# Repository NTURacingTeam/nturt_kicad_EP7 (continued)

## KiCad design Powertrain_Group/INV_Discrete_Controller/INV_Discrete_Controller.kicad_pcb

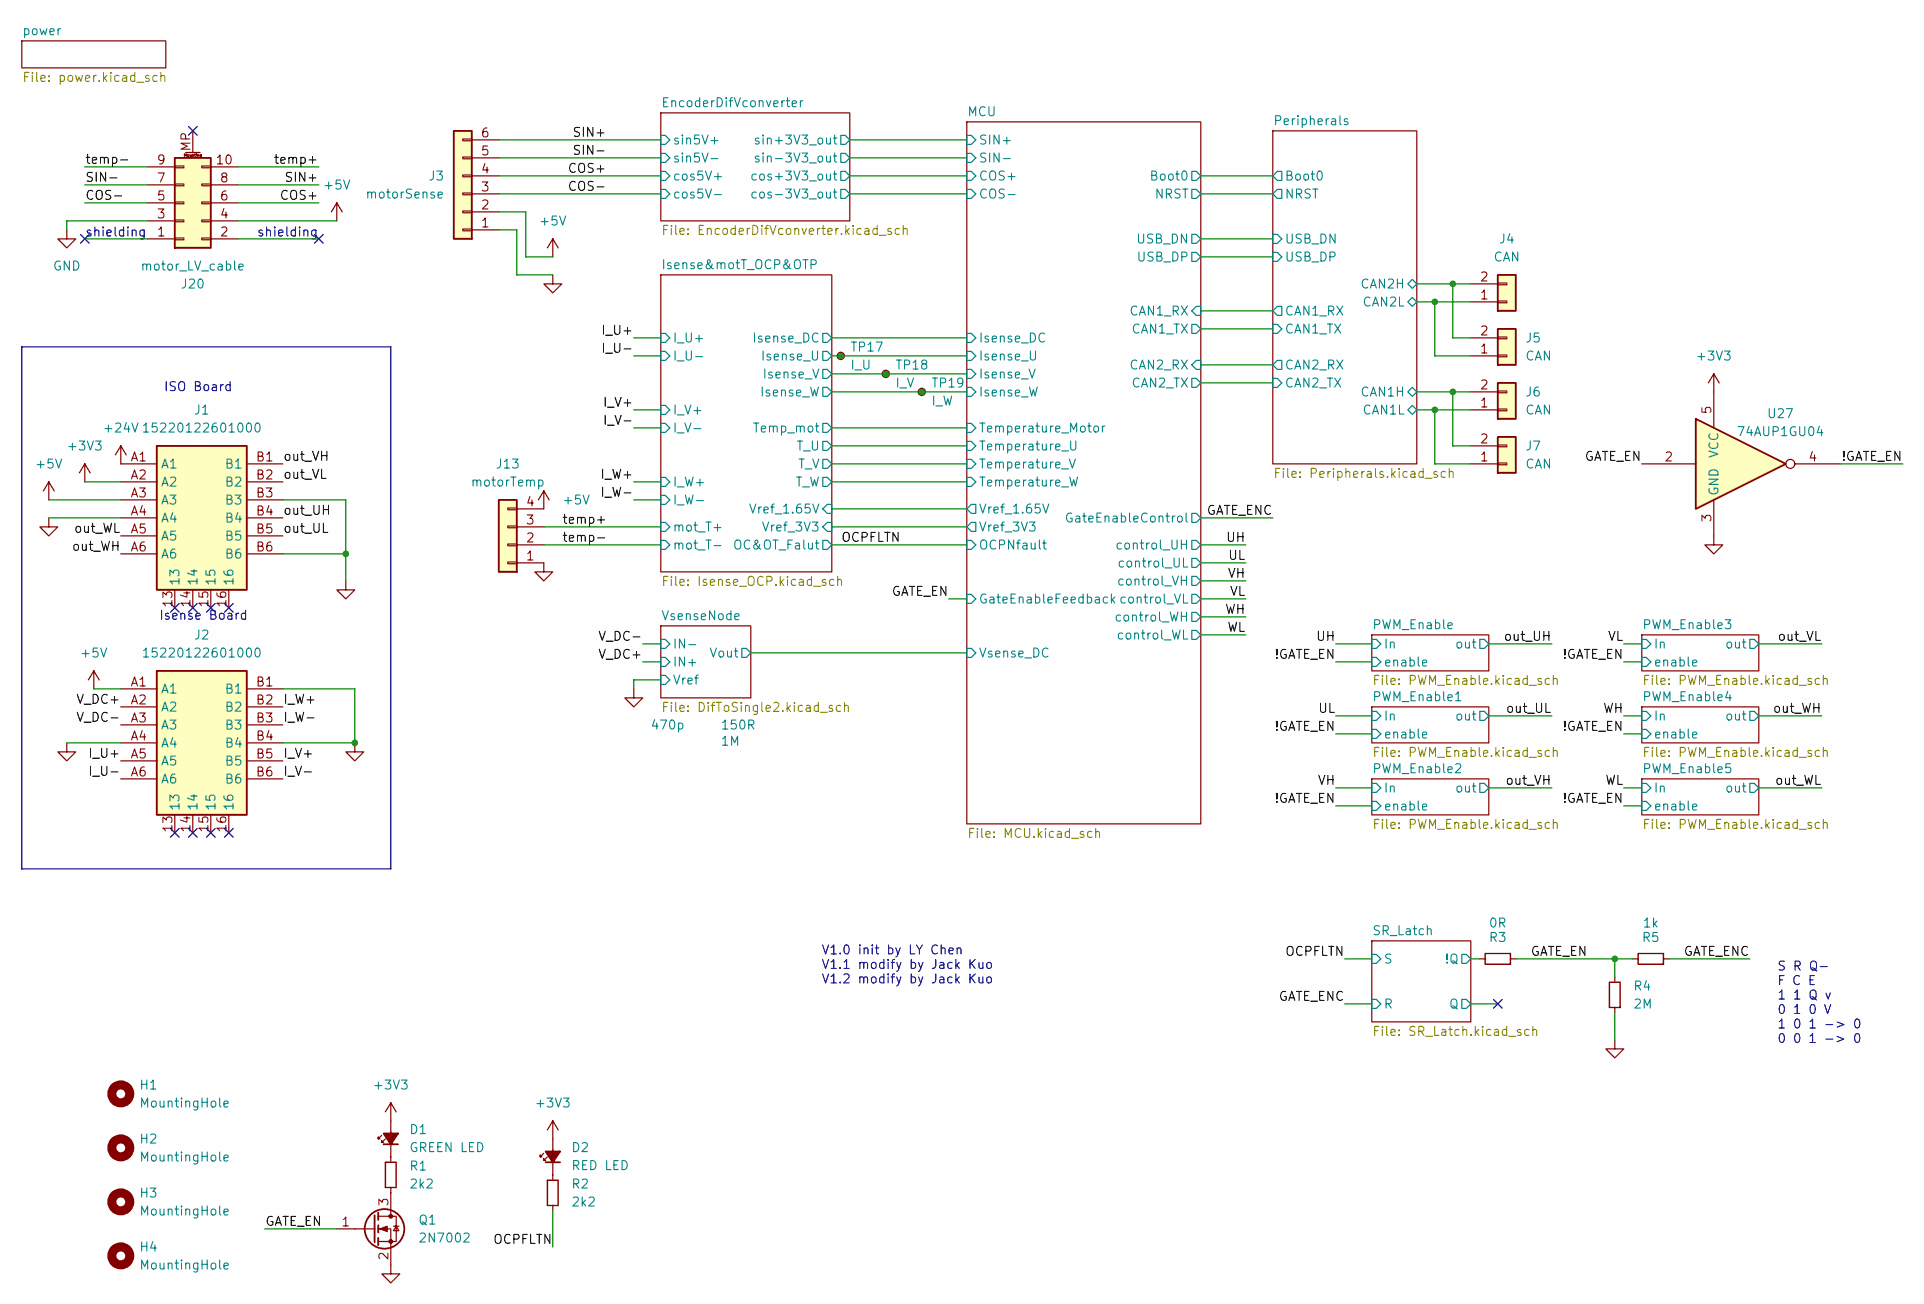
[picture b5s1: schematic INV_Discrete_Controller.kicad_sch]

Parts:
D1: GREEN LED; LED_0805_2012Metric
D2: RED LED; LED_0805_2012Metric
H1, H2, H3, H4: MountingHole; MountingHole_3.2mm_M3
J1, J2: 15220122601000; Harting_15220122601000; Mouser Part Number 617-15130122601000
J3: motorSense; JST_XH_B6B-XH-A_1x06_P2.50mm_Vertical
J4, J5, J6, J7: CAN; JST_XH_B2B-XH-A_1x02_P2.50mm_Vertical
J13: motorTemp; JST_XH_B4B-XH-A_1x04_P2.50mm_Vertical
J20: motor_LV_cable; CONN_2202010000-SD_10P_MOL
Q1: 2N7002; SOT-23
R1, R2: 2k2; R_0402_1005Metric
R3: 0R; R_0402_1005Metric
R4: 2M; R_0603_1608Metric
R5: 1k; R_0402_1005Metric
TP17: I_U; TestPoint_Pad_D1.0mm
TP18: I_V; TestPoint_Pad_D1.0mm
TP19: I_W; TestPoint_Pad_D1.0mm
U27: 74AUP1GU04; SOT-23-5

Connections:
+3V3: D1.2 (A), D2.2 (A), J1.A2, U27.5 (VCC); also elsewhere on the board
+5V: J1.A3, J2.A1, J3.2, J13.4, J20.4; also elsewhere on the board
+24V: J1.A1; also elsewhere on the board
/!GATE_EN: U27.4; also elsewhere on the board
/COS+: J3.4, J20.6; also elsewhere on the board
/COS-: J3.3, J20.5; also elsewhere on the board
/GATE_EN: Q1.1 (G), R3.1, R4.2, R5.2, U27.2; also elsewhere on the board
/GATE_ENC: R5.1; also elsewhere on the board
/I_U+: J2.A5; also elsewhere on the board
/I_U-: J2.A6; also elsewhere on the board
/I_V+: J2.B5; also elsewhere on the board
/I_V-: J2.B6; also elsewhere on the board
/I_W+: J2.B2; also elsewhere on the board
/I_W-: J2.B3; also elsewhere on the board
/Isense&motT_OCP&OTP/Isense_U: TP17.1; also elsewhere on the board
/Isense&motT_OCP&OTP/Isense_V: TP18.1; also elsewhere on the board
/Isense&motT_OCP&OTP/Isense_W: TP19.1; also elsewhere on the board
/OCPFLTN: R2.2; also elsewhere on the board
/Peripherals/CAN1H: J6.2, J7.2; also elsewhere on the board
/Peripherals/CAN1L: J6.1, J7.1; also elsewhere on the board
/Peripherals/CAN2H: J4.2, J5.2; also elsewhere on the board
/Peripherals/CAN2L: J4.1, J5.1; also elsewhere on the board
/SIN+: J3.6, J20.8; also elsewhere on the board
/SIN-: J3.5, J20.7; also elsewhere on the board
/SR_Latch/!Q: R3.2; also elsewhere on the board
/V_DC+: J2.A2; also elsewhere on the board
/V_DC-: J2.A3; also elsewhere on the board
/out_UH: J1.B4; also elsewhere on the board
/out_UL: J1.B5; also elsewhere on the board
/out_VH: J1.B1; also elsewhere on the board
/out_VL: J1.B2; also elsewhere on the board
/out_WH: J1.A6; also elsewhere on the board
/out_WL: J1.A5; also elsewhere on the board
/temp+: J13.3, J20.10; also elsewhere on the board
/temp-: J13.2, J20.9; also elsewhere on the board
GND: J1.A4, J1.B3, J1.B6, J2.A4, J2.B1, J2.B4, J3.1, J13.1, J20.3, Q1.2 (S), R4.1, U27.3 (GND); also elsewhere on the board
unnamed: D1.1 (K), R1.1
unnamed: D2.1 (K), R2.1
unnamed: Q1.3 (D), R1.2

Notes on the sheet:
shielding
V1.0 init by LY Chen V1.1 modify by Jack Kuo V1.2 modify by Jack Kuo
Isense Board
S R Q- F C E 1 1 Q v 0 1 0 V 1 0 1 -> 0 0 0 1 -> 0
ISO Board

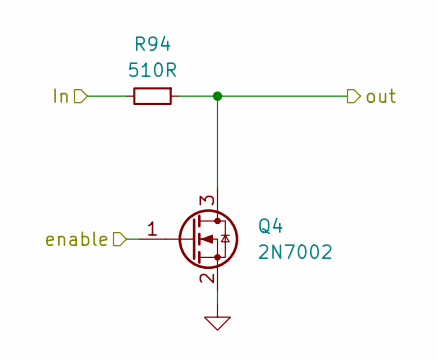
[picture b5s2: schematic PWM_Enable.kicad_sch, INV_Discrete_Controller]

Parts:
Q4: 2N7002; SOT-23
R94: 510R; R_0603_1608Metric

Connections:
/!GATE_EN: Q4.1 (G); also elsewhere on the board
/UH: R94.2; also elsewhere on the board
/out_UH: Q4.3 (D), R94.1; also elsewhere on the board
GND: Q4.2 (S); also elsewhere on the board

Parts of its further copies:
Q2, Q3, Q5, Q6, Q7: 2N7002; SOT-23
R80, R93, R98, R99, R100: 510R; R_0603_1608Metric

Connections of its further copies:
/!GATE_EN: Q2.1 (G), Q3.1 (G), Q5.1 (G), Q6.1 (G), Q7.1 (G); also elsewhere on the board
/UL: R80.2; also elsewhere on the board
/VH: R93.2; also elsewhere on the board
/VL: R98.2; also elsewhere on the board
/WH: R99.2; also elsewhere on the board
/WL: R100.2; also elsewhere on the board
/out_UL: Q2.3 (D), R80.1; also elsewhere on the board
/out_VH: Q3.3 (D), R93.1; also elsewhere on the board
/out_VL: Q5.3 (D), R98.1; also elsewhere on the board
/out_WH: Q6.3 (D), R99.1; also elsewhere on the board
/out_WL: Q7.3 (D), R100.1; also elsewhere on the board
GND: Q2.2 (S), Q3.2 (S), Q5.2 (S), Q6.2 (S), Q7.2 (S); also elsewhere on the board

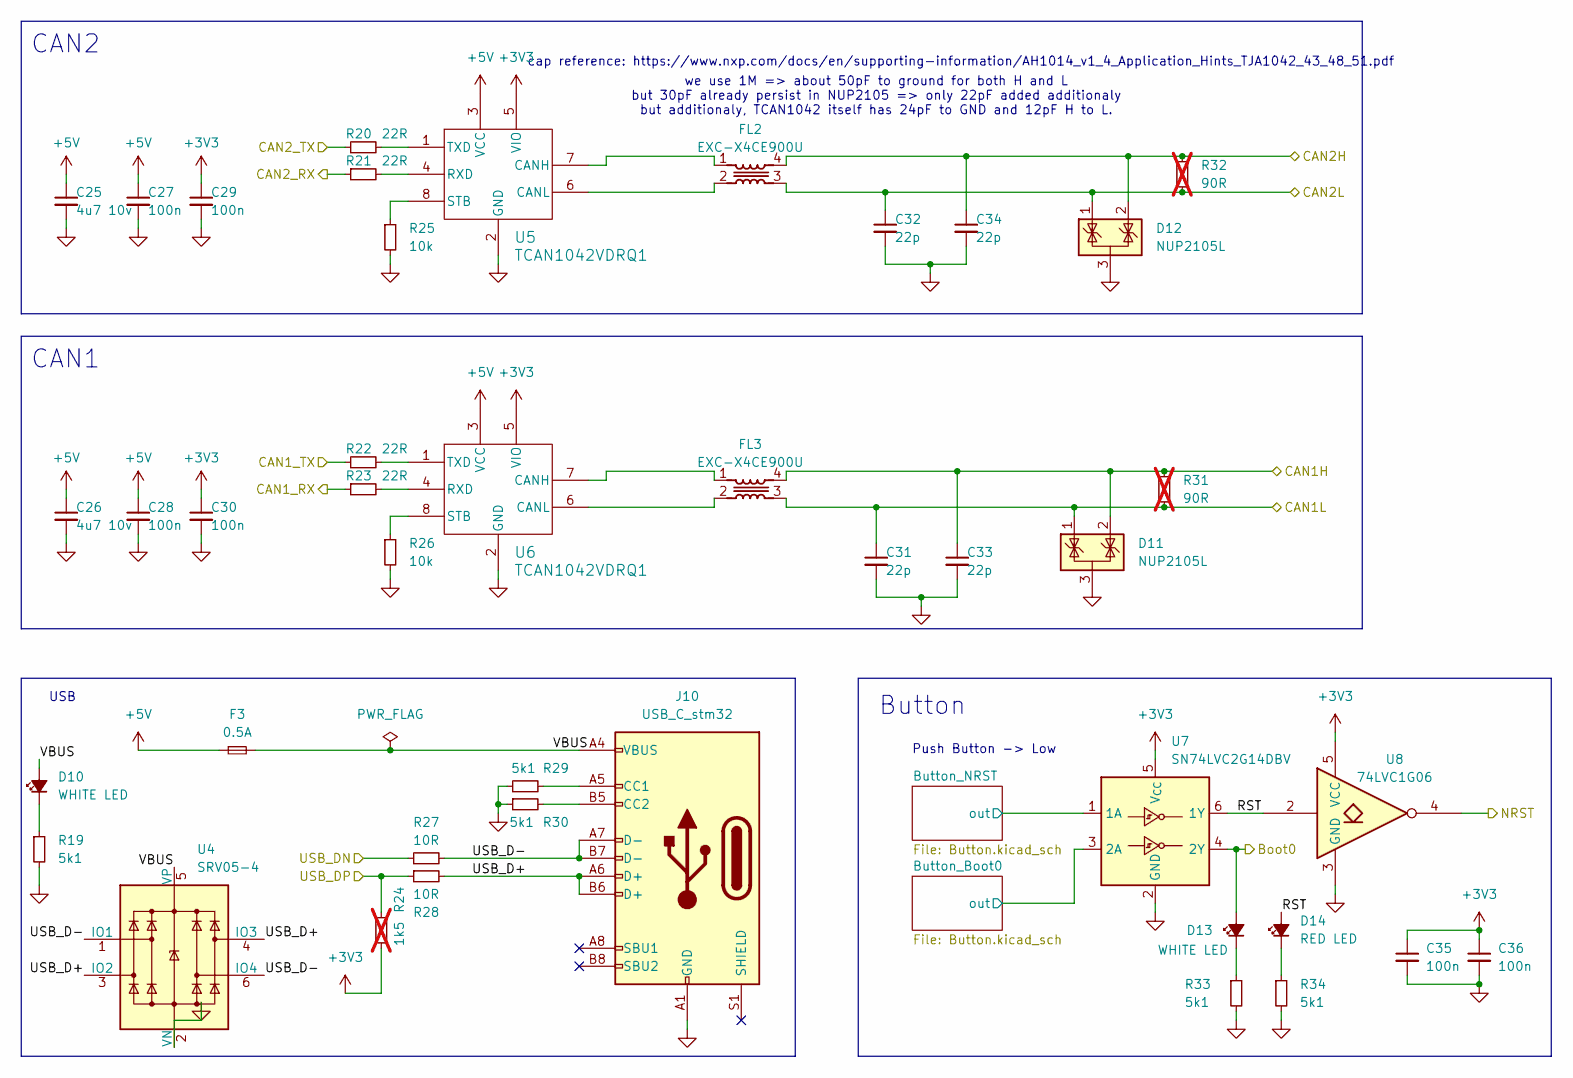
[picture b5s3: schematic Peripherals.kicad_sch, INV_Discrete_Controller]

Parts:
C25, C26: 4u7 10v; C_0402_1005Metric
C27, C28, C29, C30, C35, C36: 100n; C_0402_1005Metric
C31, C32, C33, C34: 22p; C_0402_1005Metric
D10, D13: WHITE LED; LED_0603_1608Metric
D11, D12: NUP2105L; SOT-23
D14: RED LED; LED_0603_1608Metric
F3: 0.5A; Fuse_1206_3216Metric
FL2, FL3: EXC-X4CE900U; EXCX4CE900U; Mouser Part Number 667-EXC-X4CE900U
J10: USB_C_stm32; USB_C_Receptacle_GCT_USB4105-xx-A_16P_TopMnt_Horizontal
R19, R29, R30, R33, R34: 5k1; R_0402_1005Metric
R20, R21, R22, R23: 22R; R_0402_1005Metric
R24: 1k5; R_0402_1005Metric; not fitted
R25, R26: 10k; R_0402_1005Metric
R27, R28: 10R; R_0402_1005Metric
R31, R32: 90R; R_0402_1005Metric; not fitted
U4: SRV05-4; SOT-23-6
U5, U6: TCAN1042VDRQ1; SOIC-8_3.9x4.9mm_P1.27mm
U7: SN74LVC2G14DBV; SOT-23-6
U8: 74LVC1G06; SOT-23-5

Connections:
+3V3: C29.1, C30.1, C35.1, C36.1, R24.1, U5.5 (VIO), U6.5 (VIO), U7.5 (V_{CC}), U8.5 (VCC); also elsewhere on the board
+5V: C25.1, C26.1, C27.1, C28.1, F3.1, U5.3 (VCC), U6.3 (VCC); also elsewhere on the board
/MCU/Boot0: D13.2 (A), U7.4 (2Y); also elsewhere on the board
/MCU/CAN1_RX: R23.1; also elsewhere on the board
/MCU/CAN1_TX: R22.1; also elsewhere on the board
/MCU/CAN2_RX: R21.1; also elsewhere on the board
/MCU/CAN2_TX: R20.1; also elsewhere on the board
/MCU/NRST: U8.4; also elsewhere on the board
/MCU/USB_DN: R27.1; also elsewhere on the board
/MCU/USB_DP: R24.2, R28.1; also elsewhere on the board
/Peripherals/Button_Boot0/out: U7.3 (2A); also elsewhere on the board
/Peripherals/Button_NRST/out: U7.1 (1A); also elsewhere on the board
/Peripherals/CAN1H: C33.1, D11.2 (K), FL3.4, R31.1; also elsewhere on the board
/Peripherals/CAN1L: C31.1, D11.1 (K), FL3.3, R31.2; also elsewhere on the board
/Peripherals/CAN2H: C34.1, D12.2 (K), FL2.4, R32.1; also elsewhere on the board
/Peripherals/CAN2L: C32.1, D12.1 (K), FL2.3, R32.2; also elsewhere on the board
/Peripherals/RST: D14.2 (A), U7.6 (1Y), U8.2
/Peripherals/USB_D+: J10.A6 (D+), J10.B6 (D+), R28.2, U4.3 (IO2), U4.4 (IO3)
/Peripherals/USB_D-: J10.A7 (D-), J10.B7 (D-), R27.2, U4.1 (IO1), U4.6 (IO4)
/Peripherals/VBUS: D10.2 (A), F3.2, J10.A4 (VBUS), J10.A9 (VBUS), J10.B4 (VBUS), J10.B9 (VBUS), U4.5 (VP)
GND: C25.2, C26.2, C27.2, C28.2, C29.2, C30.2, C31.2, C32.2, C33.2, C34.2, C35.2, C36.2, D11.3 (A), D12.3 (A), J10.A1 (GND), J10.A12 (GND), J10.B1 (GND), J10.B12 (GND), R19.2, R25.2, R26.2, R29.1, R30.1, R33.2, R34.2, U4.2 (VN), U5.2 (GND), U6.2 (GND), U7.2 (GND), U8.3 (GND); also elsewhere on the board
unnamed: D10.1 (K), R19.1
unnamed: D13.1 (K), R33.1
unnamed: D14.1 (K), R34.1
unnamed: J10.A5 (CC1), R29.2
unnamed: J10.B5 (CC2), R30.2
unnamed: FL2.1, U5.7 (CANH)
unnamed: FL2.2, U5.6 (CANL)
unnamed: R21.2, U5.4 (RXD)
unnamed: R25.1, U5.8 (STB)
unnamed: R20.2, U5.1 (TXD)
unnamed: FL3.1, U6.7 (CANH)
unnamed: FL3.2, U6.6 (CANL)
unnamed: R23.2, U6.4 (RXD)
unnamed: R26.1, U6.8 (STB)
unnamed: R22.2, U6.1 (TXD)

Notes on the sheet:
Push Button -> Low
Button
USB
we use 1M => about 50pF to ground for both H and L but 30pF already persist in NUP2105 => only 22pF added additionaly but additionaly, TCAN1042 itself has 24pF to GND and 12pF H to L.
CAN2
CAN1
cap reference: https://www.nxp.com/docs/en/supporting-information/AH1014_v1_4_Application_Hints_TJA1042_43_48_51.pdf

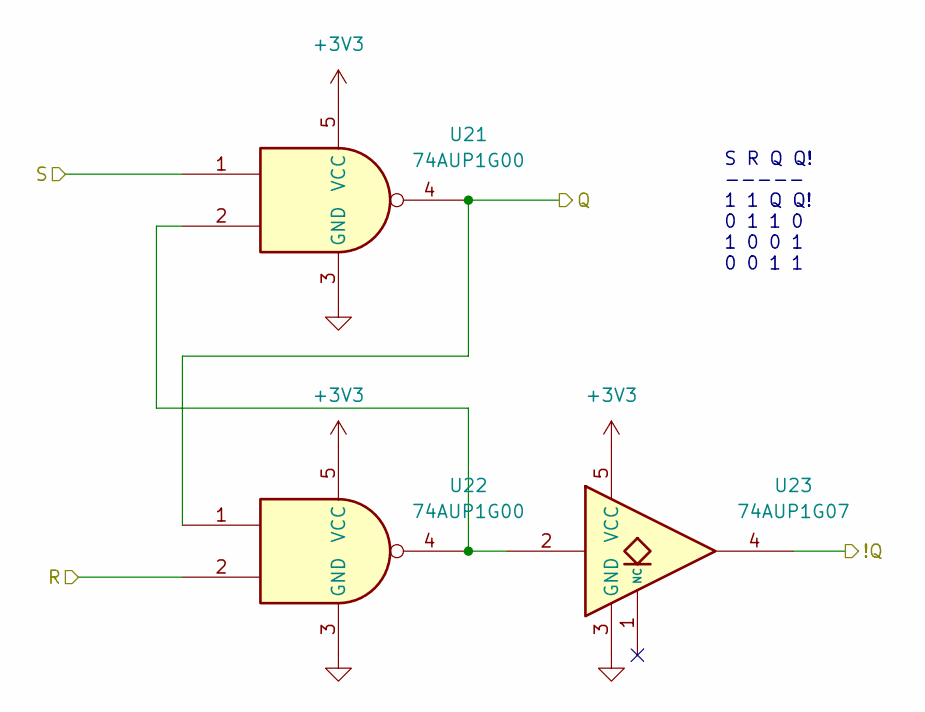
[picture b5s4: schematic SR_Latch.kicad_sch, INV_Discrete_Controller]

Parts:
U21, U22: 74AUP1G00; SOT-23-5
U23: 74AUP1G07; SOT-23-5

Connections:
+3V3: U21.5 (VCC), U22.5 (VCC), U23.5 (VCC); also elsewhere on the board
/GATE_ENC: U22.2; also elsewhere on the board
/OCPFLTN: U21.1; also elsewhere on the board
/SR_Latch/!Q: U23.4; also elsewhere on the board
/SR_Latch/Q: U21.4, U22.1
GND: U21.3 (GND), U22.3 (GND), U23.3 (GND); also elsewhere on the board
unnamed: U21.2, U22.4, U23.2

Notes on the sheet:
S R Q Q! ----- 1 1 Q Q! 0 1 1 0 1 0 0 1 0 0 1 1

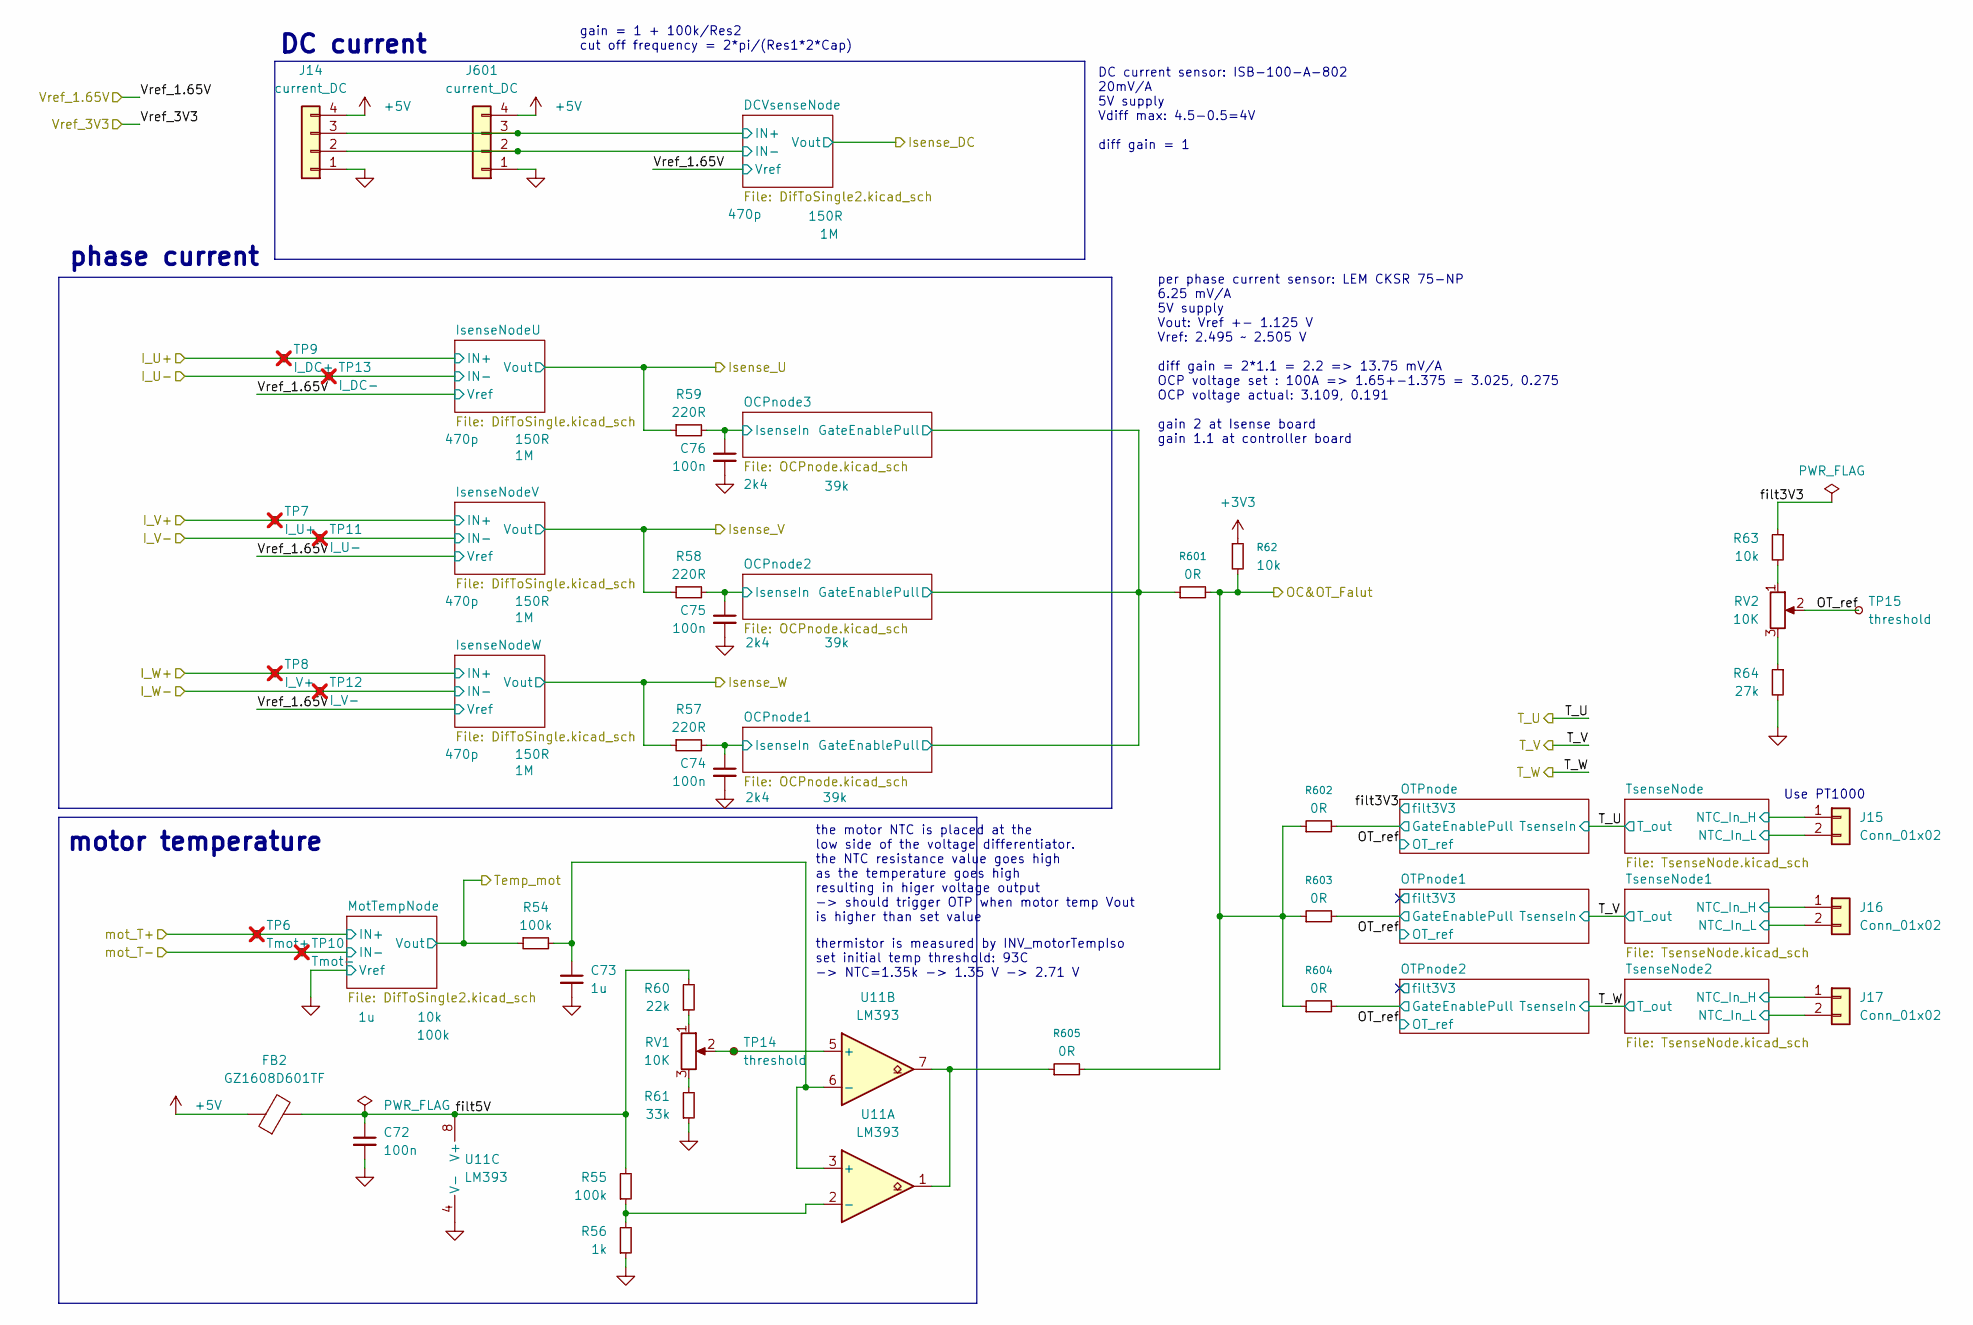
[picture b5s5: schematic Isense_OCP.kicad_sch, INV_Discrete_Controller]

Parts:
C72, C74, C75, C76: 100n; C_0402_1005Metric
C73: 1u; C_0402_1005Metric
FB2: GZ1608D601TF; C_0603_1608Metric
J14: current_DC; JST_XH_B4B-XH-A_1x04_P2.50mm_Vertical; Part Number 1-0401FBV0T
J15, J16, J17: Conn_01x02; JST_PH_B2B-PH-K_1x02_P2.00mm_Vertical
J601: current_DC; JST_PH_B4B-PH-K_1x04_P2.00mm_Vertical; Part Number 1-0401FBV0T
R54, R55: 100k; R_0402_1005Metric
R56: 1k; R_0402_1005Metric
R57, R58, R59: 220R; R_0402_1005Metric
R60: 22k; R_0402_1005Metric
R61: 33k; R_0402_1005Metric
R62, R63: 10k; R_0402_1005Metric
R64: 27k; R_0402_1005Metric
R601, R602, R603, R604, R605: 0R; R_0402_1005Metric
RV1, RV2: 10K; Potentiometer_Bourns_3296W_Horizontal
TP6: Tmot+; TestPoint_Pad_D1.0mm; not fitted
TP7: I_U+; TestPoint_Pad_D1.0mm; not fitted
TP8: I_V+; TestPoint_Pad_D1.0mm; not fitted
TP9: I_DC+; TestPoint_Pad_D1.0mm; not fitted
TP10: Tmot-; TestPoint_Pad_D1.0mm; not fitted
TP11: I_U-; TestPoint_Pad_D1.0mm; not fitted
TP12: I_V-; TestPoint_Pad_D1.0mm; not fitted
TP13: I_DC-; TestPoint_Pad_D1.0mm; not fitted
TP14, TP15: threshold; TestPoint_Pad_D1.0mm
U11: LM393; SOIC-8_3.9x4.9mm_P1.27mm

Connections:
+3V3: R62.1; also elsewhere on the board
+5V: FB2.1, J14.4, J601.4; also elsewhere on the board
/Isense&motT_OCP&OTP/DCVsenseNode/IN+: J14.3, J601.3; also elsewhere on the board
/Isense&motT_OCP&OTP/DCVsenseNode/IN-: J14.2, J601.2; also elsewhere on the board
/Isense&motT_OCP&OTP/Isense_U: R59.1; also elsewhere on the board
/Isense&motT_OCP&OTP/Isense_V: R58.1; also elsewhere on the board
/Isense&motT_OCP&OTP/Isense_W: R57.1; also elsewhere on the board
/Isense&motT_OCP&OTP/OCPnode1/GateEnablePull: R601.1; also elsewhere on the board
/Isense&motT_OCP&OTP/OCPnode1/IsenseIn: C74.1, R57.2; also elsewhere on the board
/Isense&motT_OCP&OTP/OCPnode2/IsenseIn: C75.1, R58.2; also elsewhere on the board
/Isense&motT_OCP&OTP/OCPnode3/IsenseIn: C76.1, R59.2; also elsewhere on the board
/Isense&motT_OCP&OTP/OTPnode1/GateEnablePull: R603.2; also elsewhere on the board
/Isense&motT_OCP&OTP/OTPnode2/GateEnablePull: R604.2; also elsewhere on the board
/Isense&motT_OCP&OTP/OTPnode/GateEnablePull: R602.2; also elsewhere on the board
/Isense&motT_OCP&OTP/OT_ref: RV2.2, TP15.1; also elsewhere on the board
/Isense&motT_OCP&OTP/Temp_mot: R54.1; also elsewhere on the board
/Isense&motT_OCP&OTP/TsenseNode1/NTC_In_H: J16.1; also elsewhere on the board
/Isense&motT_OCP&OTP/TsenseNode2/NTC_In_H: J17.1; also elsewhere on the board
/Isense&motT_OCP&OTP/TsenseNode/NTC_In_H: J15.1; also elsewhere on the board
/Isense&motT_OCP&OTP/filt3V3: R63.1; also elsewhere on the board
/Isense&motT_OCP&OTP/filt5V: C72.1, FB2.2, R55.2, R60.2, U11.8 (V+)
/OCPFLTN: R62.2, R601.2, R602.1, R603.1, R604.1, R605.2; also elsewhere on the board
GND: C72.2, C73.2, C74.2, C75.2, C76.2, J14.1, J15.2, J16.2, J17.2, J601.1, R56.1, R61.1, R64.2, U11.4 (V-); also elsewhere on the board
unnamed: R60.1, RV1.1
unnamed: R61.2, RV1.3
unnamed: R63.2, RV2.1
unnamed: R64.1, RV2.3
unnamed: R605.1, U11.1, U11.7
unnamed: C73.1, R54.2, U11.3 (+), U11.6 (-)
unnamed: R55.1, R56.2, U11.2 (-)
unnamed: RV1.2, TP14.1, U11.5 (+)

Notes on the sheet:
the motor NTC is placed at the low side of the voltage differentiator. the NTC resistance value goes high as the temperature goes high resulting in higer voltage output -> should trigger OTP when motor temp Vout is higher than set value
DC current sensor: ISB-100-A-802 20mV/A 5V supply Vdiff max: 4.5-0.5=4V diff gain = 1
Use PT1000
phase current
DC current
motor temperature
thermistor is measured by INV_motorTempIso set initial temp threshold: 93C -> NTC=1.35k -> 1.35 V -> 2.71 V
per phase current sensor: LEM CKSR 75-NP 6.25 mV/A 5V supply Vout: Vref +- 1.125 V Vref: 2.495 ~ 2.505 V diff gain = 2*1.1 = 2.2 => 13.75 mV/A OCP voltage set : 100A => 1.65+-1.375 = 3.025, 0.275 OCP voltage actual: 3.109, 0.191 gain 2 at Isense board gain 1.1 at controller board
gain = 1 + 100k/Res2 cut off frequency = 2*pi/(Res1*2*Cap)

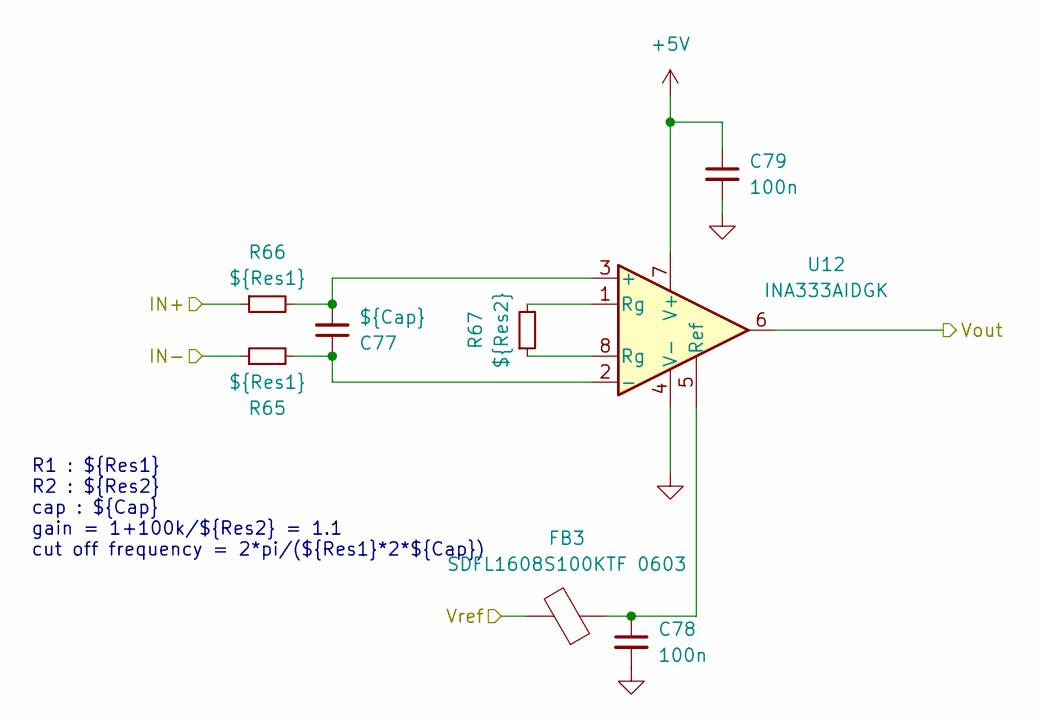
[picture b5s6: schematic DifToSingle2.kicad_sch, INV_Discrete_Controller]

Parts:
C77: ${Cap}; C_0402_1005Metric
C78, C79: 100n; C_0402_1005Metric
FB3: SDFL1608S100KTF 0603; C_0603_1608Metric
R65, R66: ${Res1}; R_0402_1005Metric
R67: ${Res2}; R_0402_1005Metric
U12: INA333AIDGK; VSSOP-8_3x3mm_P0.65mm

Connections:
+5V: C79.1, U12.7 (V+); also elsewhere on the board
/Isense&motT_OCP&OTP/DCVsenseNode/IN+: R66.1; also elsewhere on the board
/Isense&motT_OCP&OTP/DCVsenseNode/IN-: R65.1; also elsewhere on the board
/Isense&motT_OCP&OTP/Isense_DC: U12.6; also elsewhere on the board
/Isense&motT_OCP&OTP/Vref_1.65V: FB3.2; also elsewhere on the board
GND: C78.2, C79.2, U12.4 (V-); also elsewhere on the board
unnamed: R67.1, U12.8 (Rg)
unnamed: R67.2, U12.1 (Rg)
unnamed: C77.2, R66.2, U12.3 (+)
unnamed: C77.1, R65.2, U12.2 (-)
unnamed: C78.1, FB3.1, U12.5 (Ref)

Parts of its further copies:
C90, C91, C93, C94: 100n; C_0402_1005Metric
FB10, FB11: SDFL1608S100KTF 0603; C_0603_1608Metric
U25, U29: INA333AIDGK; VSSOP-8_3x3mm_P0.65mm

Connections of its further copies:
+5V: C91.1, C94.1, U25.7 (V+), U29.7 (V+); also elsewhere on the board
/Isense&motT_OCP&OTP/Temp_mot: U25.6; also elsewhere on the board
/MCU/Vsense_DC: U29.6; also elsewhere on the board
GND: C90.2, C91.2, C93.2, C94.2, FB10.2, FB11.2, U25.4 (V-), U29.4 (V-); also elsewhere on the board
unnamed 166: U25.8 (Rg); also elsewhere on the board
unnamed 167: U25.1 (Rg); also elsewhere on the board
unnamed 168: U29.8 (Rg); also elsewhere on the board
unnamed 169: U29.1 (Rg); also elsewhere on the board
unnamed 209: U25.3 (+); also elsewhere on the board
unnamed 210: U25.2 (-); also elsewhere on the board
unnamed: C90.1, FB10.1, U25.5 (Ref)
unnamed 212: U29.3 (+); also elsewhere on the board
unnamed 213: U29.2 (-); also elsewhere on the board
unnamed: C93.1, FB11.1, U29.5 (Ref)

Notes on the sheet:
R1 : ${Res1} R2 : ${Res2} cap : ${Cap} gain = 1+100k/${Res2} = 1.1 cut off frequency = 2*pi/(${Res1}*2*${Cap})
